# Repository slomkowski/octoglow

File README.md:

# Octoglow VFD - Fallout-inspired post-apocalyptic display

Design files of Octoglow, the post-apocalyptic desktop display device. Detailed article [published on my website](https://slomkowski.eu/octoglow-vfd-fallout-inspired-display/).

(C) Michał Słomkowski

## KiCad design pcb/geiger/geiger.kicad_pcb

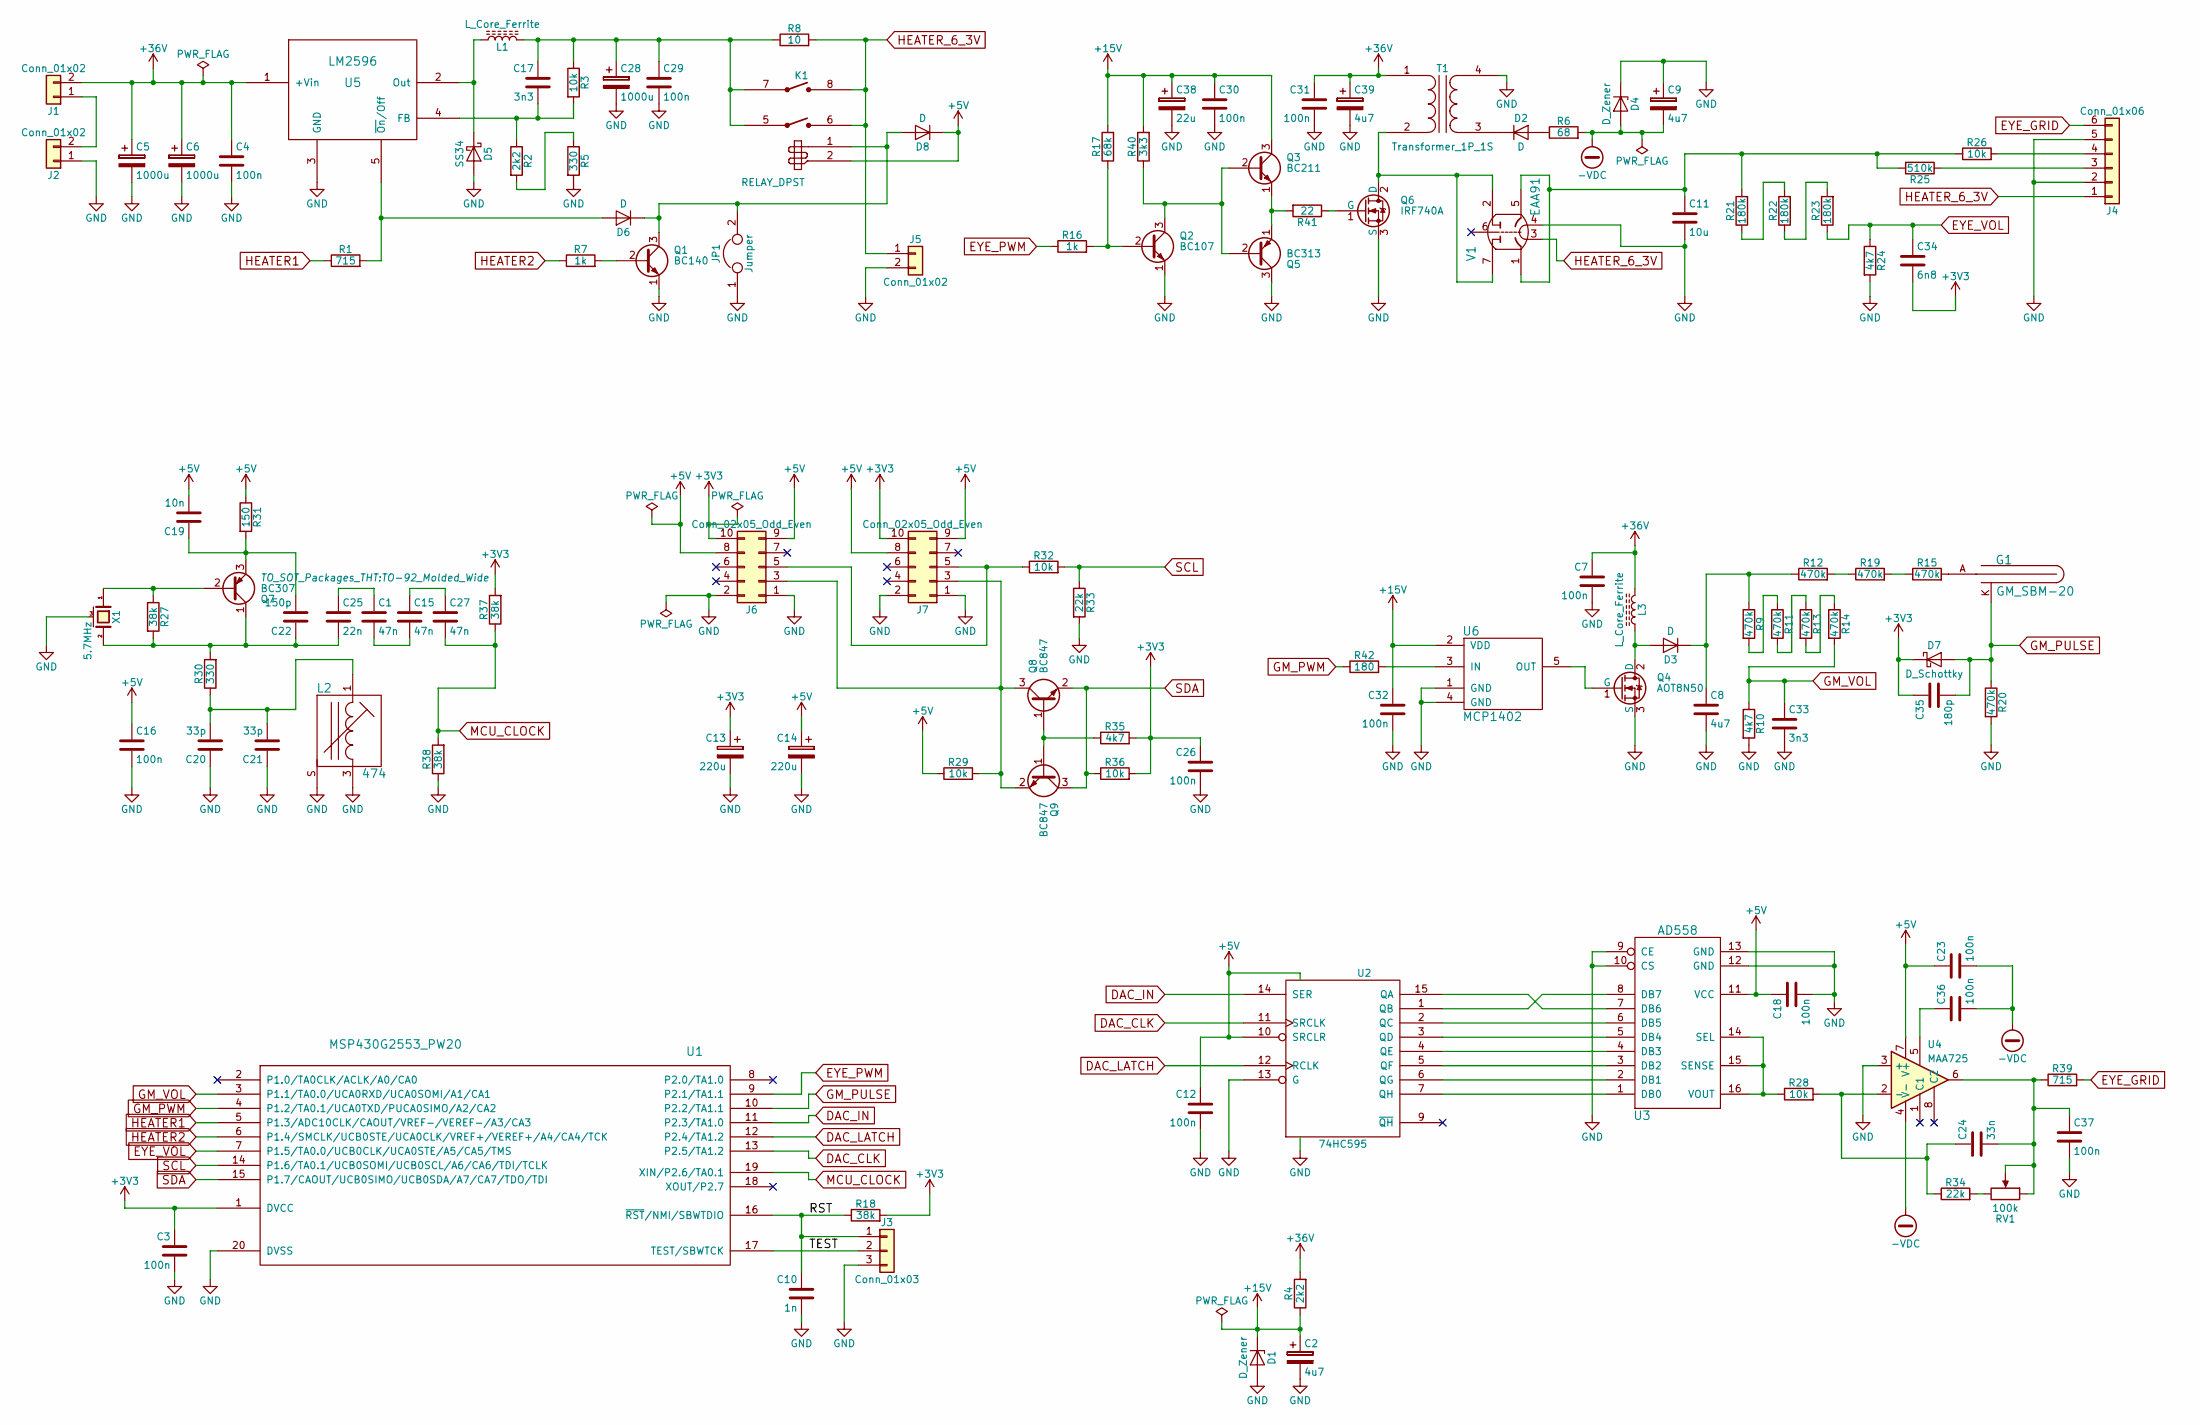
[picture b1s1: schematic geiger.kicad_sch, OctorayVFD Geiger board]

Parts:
C1, C15, C27: 47n; C_Disc_D5.0mm_W2.5mm_P5.00mm
C2: 4u7; CP_Radial_D6.3mm_P2.50mm
C3, C4, C7, C12, C16, C18, C23, C26, C29, C30, C31, C32, C36, C37: 100n; C_1206_HandSoldering
C5, C6: 1000u; CP_Radial_D16.0mm_P7.50mm
C8: 4u7; C_Rect_L33.0mm_W13.0mm_P27.50mm_MKS4
C9, C39: 4u7; CP_Tantalum_Case-D_EIA-7343-31_Hand
C10: 1n; C_0805_HandSoldering
C11: 10u; C_Rect_L33.0mm_W13.0mm_P27.50mm_MKS4
C13, C14: 220u; CP_Radial_D13.0mm_P5.00mm
C17, C33: 3n3; C_1206_HandSoldering
C19: 10n; C_Disc_D5.0mm_W2.5mm_P5.00mm
C20, C21: 33p; C_Disc_D5.0mm_W2.5mm_P5.00mm
C22: 150p; C_Disc_D5.0mm_W2.5mm_P5.00mm
C24: 33n; C_Disc_D11.0mm_W5.0mm_P5.00mm
C25: 22n; C_Disc_D5.0mm_W2.5mm_P5.00mm
C28: 1000u; CP_Radial_D8.0mm_P3.50mm
C34: 6n8; C_Rect_L9.0mm_W3.2mm_P7.50mm_MKT
C35: 180p; C_Rect_L9.0mm_W3.2mm_P7.50mm_MKT
C38: 22u; CP_Tantalum_Case-B_EIA-3528-21_Hand
D1, D4: D_Zener; D_DO-41_SOD81_P2.54mm_Vertical_AnodeUp
D2, D3: D; D_SMB
D5: SS34; D_SMA-SMB_Universal_Handsoldering
D6, D8: D; D_DO-41_SOD81_P12.70mm_Horizontal
D7: D_Schottky; D_DO-35_SOD27_P10.16mm_Horizontal
G1: GM_SBM-20
J1, J2, J5: Conn_01x02; TerminalBlock_Pheonix_MKDS1.5-2pol
J3: Conn_01x03; Pin_Header_Straight_1x03_Pitch2.54mm
J4: Conn_01x06; TerminalBlock_Pheonix_PT-3.5mm_6pol
J6, J7: Conn_02x05_Odd_Even; Pin_Header_Straight_2x05_Pitch2.54mm
JP1: Jumper; Pin_Header_Straight_1x02_Pitch2.54mm
K1: RELAY_DPST; RELAY_DPST_Telfa_K-8
L1: L_Core_Ferrite; Choke_SMD_12x12mm_h8mm
L2: 474; L_7x7_II
L3: L_Core_Ferrite; F1001_coil
Q1: BC140; TO-39-3
Q2: BC107; TO-18-3
Q3: BC211; TO-39-3
Q4: AOT8N50; TO-220-3_Vertical
Q5: BC313; TO-39-3
Q6: IRF740A; TO-220-3_Vertical
Q7: BC307; TO-92_Molded_Wide
Q8, Q9: BC847; SOT-23
R1: 715; R_Axial_DIN0411_L9.9mm_D3.6mm_P12.70mm_Horizontal
R2: 2k2; R_1206_HandSoldering
R3, R29, R32, R36: 10k; R_1206_HandSoldering
R4: 2k2; R_Axial_DIN0207_L6.3mm_D2.5mm_P10.16mm_Horizontal
R5: 330; R_1206_HandSoldering
R6: 68; R_Axial_DIN0309_L9.0mm_D3.2mm_P12.70mm_Horizontal
R7, R16: 1k; R_Axial_DIN0207_L6.3mm_D2.5mm_P10.16mm_Horizontal
R8: 10; R_Axial_DIN0617_L17.0mm_D6.0mm_P30.48mm_Horizontal
R9, R11, R13, R14, R20: 470k; R_1206_HandSoldering
R10, R24, R35: 4k7; R_1206_HandSoldering
R12, R15, R19: 470k; R_Axial_DIN0309_L9.0mm_D3.2mm_P12.70mm_Horizontal
R17: 68k; R_Axial_DIN0207_L6.3mm_D2.5mm_P10.16mm_Horizontal
R18, R27, R37, R38: 38k; R_1206_HandSoldering
R21, R22, R23: 180k; R_0805_HandSoldering
R25: 510k; R_Axial_DIN0309_L9.0mm_D3.2mm_P15.24mm_Horizontal
R26: 10k; R_Axial_DIN0309_L9.0mm_D3.2mm_P15.24mm_Horizontal
R28: 10k; R_Axial_DIN0207_L6.3mm_D2.5mm_P10.16mm_Horizontal
R30: 330; R_Axial_DIN0207_L6.3mm_D2.5mm_P10.16mm_Horizontal
R31: 150; R_Axial_DIN0207_L6.3mm_D2.5mm_P10.16mm_Horizontal
R33: 22k; R_1206_HandSoldering
R34: 22k; R_Axial_DIN0207_L6.3mm_D2.5mm_P10.16mm_Horizontal
R39: 715; R_Axial_DIN0309_L9.0mm_D3.2mm_P12.70mm_Horizontal
R40: 3k3; R_Axial_DIN0207_L6.3mm_D2.5mm_P10.16mm_Horizontal
R41: 22; R_Axial_DIN0309_L9.0mm_D3.2mm_P12.70mm_Horizontal
R42: 180; R_Axial_DIN0309_L9.0mm_D3.2mm_P15.24mm_Horizontal
RV1: 100k; Potentiometer_Trimmer_Bourns_3006P
T1: Transformer_1P_1S; F1001_trans
U1: MSP430G2553_PW20; DIP-20_W7.62mm_LongPads
U2: 74HC595; DIP-16_W7.62mm_LongPads
U3: AD558; DIP-16_W7.62mm_LongPads
U4: MAA725; TO-5-8_H08C
U5: LM2596; TO-263-5_TabPin3
U6: MCP1402; SOT-23-5_HandSoldering
V1: EAA91; HEPTAL1
X1: 5.7MHz; glass_xtal

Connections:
+3V3: C3.1, C13.1, C26.1, C34.2, C35.1, D7.1 (K), J6.10, J7.10, R18.2, R35.2, R36.2, R37.2, U1.1 (DVCC)
+5V: C12.1, C14.1, C16.1, C18.1, C19.2, C23.1, D8.1 (K), J6.8, J6.9, J7.8, J7.9, K1.2, R29.1, R31.1, U2.10 (SRCLR), U2.16 (VCC), U3.11 (VCC), U4.7 (V+)
+15V: C2.1, C30.1, C32.1, C38.1, D1.1 (K), Q3.3 (C), R4.1, R17.2, R40.2, U6.2 (VDD)
+36V: C4.1, C5.1, C6.1, C7.1, C31.1, C39.1, J1.2, L3.2, R4.2, T1.1 (AA), U5.1 (+Vin)
-VDC: C9.2, C23.2, C36.2, D4.2 (A), R6.2, U4.4 (V-)
/RST: C10.1, J3.1, R18.1, U1.16 (~RST/NMI/SBWTDIO)
/TEST: J3.2, U1.17 (TEST/SBWTCK)
DAC_CLK: U1.13 (P2.5/TA1.2), U2.11 (SRCLK)
DAC_IN: U1.11 (P2.3/TA1.0), U2.14 (SER)
DAC_LATCH: U1.12 (P2.4/TA1.2), U2.12 (RCLK)
EYE_GRID: J4.6, R39.2
EYE_PWM: R16.1, U1.9 (P2.1/TA1.1)
EYE_VOL: C34.1, R23.1, R24.1, U1.7 (P1.5/TA0.0/UCB0CLK/UCA0STE/A5/CA5/TMS)
GM_PULSE: C35.2, D7.2 (A), G1.K, R20.1, U1.10 (P2.2/TA1.1)
GM_PWM: R42.1, U1.4 (P1.2/TA0.1/UCA0TXD/PUCA0SIMO/A2/CA2)
GM_VOL: C33.1, R10.1, R14.2, U1.3 (P1.1/TA0.0/UCA0RXD/UCA0SOMI/A1/CA1)
GND: C2.2, C3.2, C4.2, C5.2, C6.2, C7.2, C8.2, C9.1, C10.2, C11.2, C12.2, C13.2, C14.2, C16.2, C18.2, C20.1, C21.1, C26.2, C28.2, C29.2, C30.2, C31.2, C32.2, C33.2, C37.2, C38.2, C39.2, D1.2 (A), D4.1 (K), D5.2 (A), J2.1, J3.3, J4.2, J4.5, J5.2, J6.1, J6.2, J7.1, J7.2, JP1.1, L2.3, L2.S, Q1.1 (E), Q2.1 (E), Q4.3 (S), Q5.3 (C), Q6.3 (S), R5.2, R10.2, R20.2, R24.2, R33.2, R38.1, T1.4 (SB), U1.20 (DVSS), U2.8 (GND), U2.13 (G), U3.9 (CE), U3.10 (CS), U3.12 (GND), U3.13 (GND), U4.3 (+), U5.3 (GND), U6.1 (GND), U6.4 (GND), V1.4, X1.3 (case)
HEATER1: R1.1, U1.5 (P1.3/ADC10CLK/CAOUT/VREF-/VEREF-/A3/CA3)
HEATER2: R7.1, U1.6 (P1.4/SMCLK/UCB0STE/UCA0CLK/VREF+/VEREF+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)
HEATER_6_3V: J4.1, J5.1, K1.6, K1.8, R8.2, V1.3
MCU_CLOCK: C27.2, R37.1, R38.2, U1.19 (XIN/P2.6/TA0.1)
unnamed: C1.1, C25.1
unnamed: C1.2, C15.2
unnamed: C11.1, R21.2, R25.2, R26.1, V1.1, V1.5
unnamed: C15.1, C27.1
unnamed: C17.1, C28.1, C29.1, K1.5, K1.7, L1.2, R3.1, R8.1
unnamed: C20.2, C21.2, L2.1, R30.1
unnamed: C24.2, C37.1, R39.1, RV1.1, RV1.2, U4.6
unnamed: C36.1, U4.5
unnamed: D2.2 (A), R6.1
unnamed: D2.1 (K), T1.3 (SA)
unnamed: D3.2 (A), L3.1, Q4.2 (D)
unnamed: C8.1, D3.1 (K), R9.1, R12.1
unnamed: D5.1 (K), L1.1, U5.2 (Out)
unnamed: D6.2 (A), R1.2, U5.5 (~On/Off)
unnamed: D6.1 (K), D8.2 (A), JP1.2, K1.1, Q1.3 (C)
unnamed: G1.A, R15.2
unnamed: J1.1, J2.2
unnamed: J4.3, R25.1
unnamed: J4.4, R26.2
unnamed: J6.3, J7.3, Q8.3 (C), Q9.2 (E), R29.2
unnamed: J6.5, J7.5, R32.1
unnamed: Q1.2 (B), R7.2
unnamed: Q2.2 (B), R16.2, R17.1
unnamed: Q2.3 (C), Q3.2 (B), Q5.2 (B), R40.1
unnamed: Q3.1 (E), Q5.1 (E), R41.2
unnamed: Q4.1 (G), U6.5 (OUT)
unnamed: Q6.2 (D), T1.2 (AB), V1.2, V1.7
unnamed: Q6.1 (G), R41.1
unnamed: Q7.2 (B), R27.1, X1.1
unnamed: C22.1, C25.2, Q7.1 (C), R27.2, R30.2, X1.2
unnamed: C19.1, C22.2, Q7.3 (E), R31.2
unnamed: Q8.1 (B), Q9.1 (B), R35.1
unnamed: R2.2, R5.1
unnamed: R9.2, R11.1
unnamed: R11.2, R13.1
unnamed: R12.2, R19.1
unnamed: R13.2, R14.1
unnamed: R15.1, R19.2
unnamed: R21.1, R22.2
unnamed: R22.1, R23.2
unnamed: R34.2, RV1.3
unnamed: U2.15 (QA), U3.7 (DB6)
unnamed: U2.1 (QB), U3.8 (DB7)
unnamed: U2.2 (QC), U3.6 (DB5)
unnamed: U2.3 (QD), U3.5 (DB4)
unnamed: U2.4 (QE), U3.4 (DB3)
unnamed: U2.5 (QF), U3.3 (DB2)
unnamed: U2.6 (QG), U3.2 (DB1)
unnamed: U2.7 (QH), U3.1 (DB0)
unnamed: R28.1, U3.14 (SEL), U3.15 (SENSE), U3.16 (VOUT)
unnamed: C24.1, R28.2, R34.1, U4.2 (-)
unnamed: C17.2, R2.1, R3.2, U5.4 (FB)
unnamed: R42.2, U6.3 (IN)
SCL: R32.2, R33.1, U1.14 (P1.6/TA0.1/UCB0SOMI/UCB0SCL/A6/CA6/TDI/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)
SDA: Q8.2 (E), Q9.3 (C), R36.1, U1.15 (P1.7/CAOUT/UCB0SIMO/UCB0SDA/A7/CA7/TDO/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)

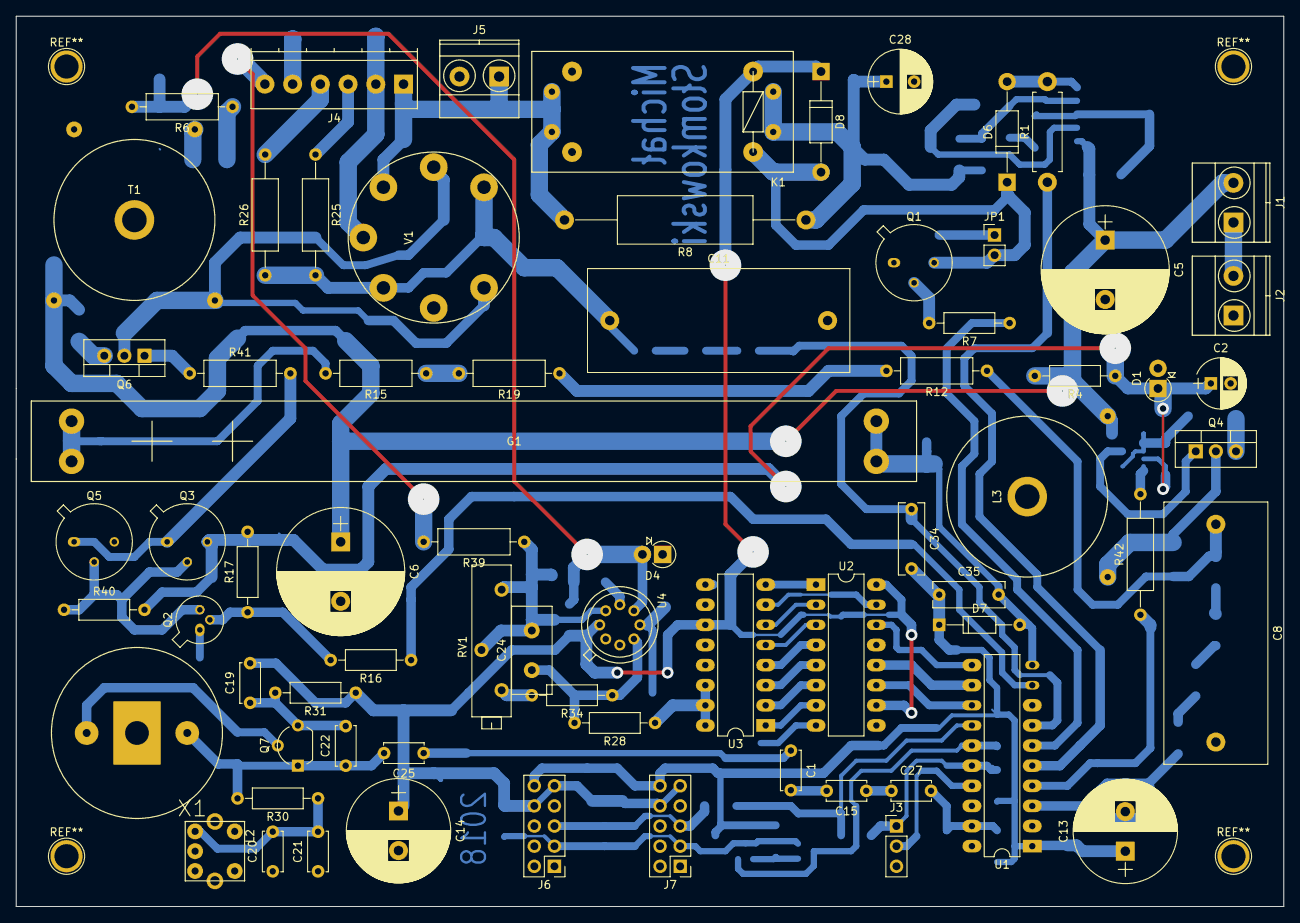
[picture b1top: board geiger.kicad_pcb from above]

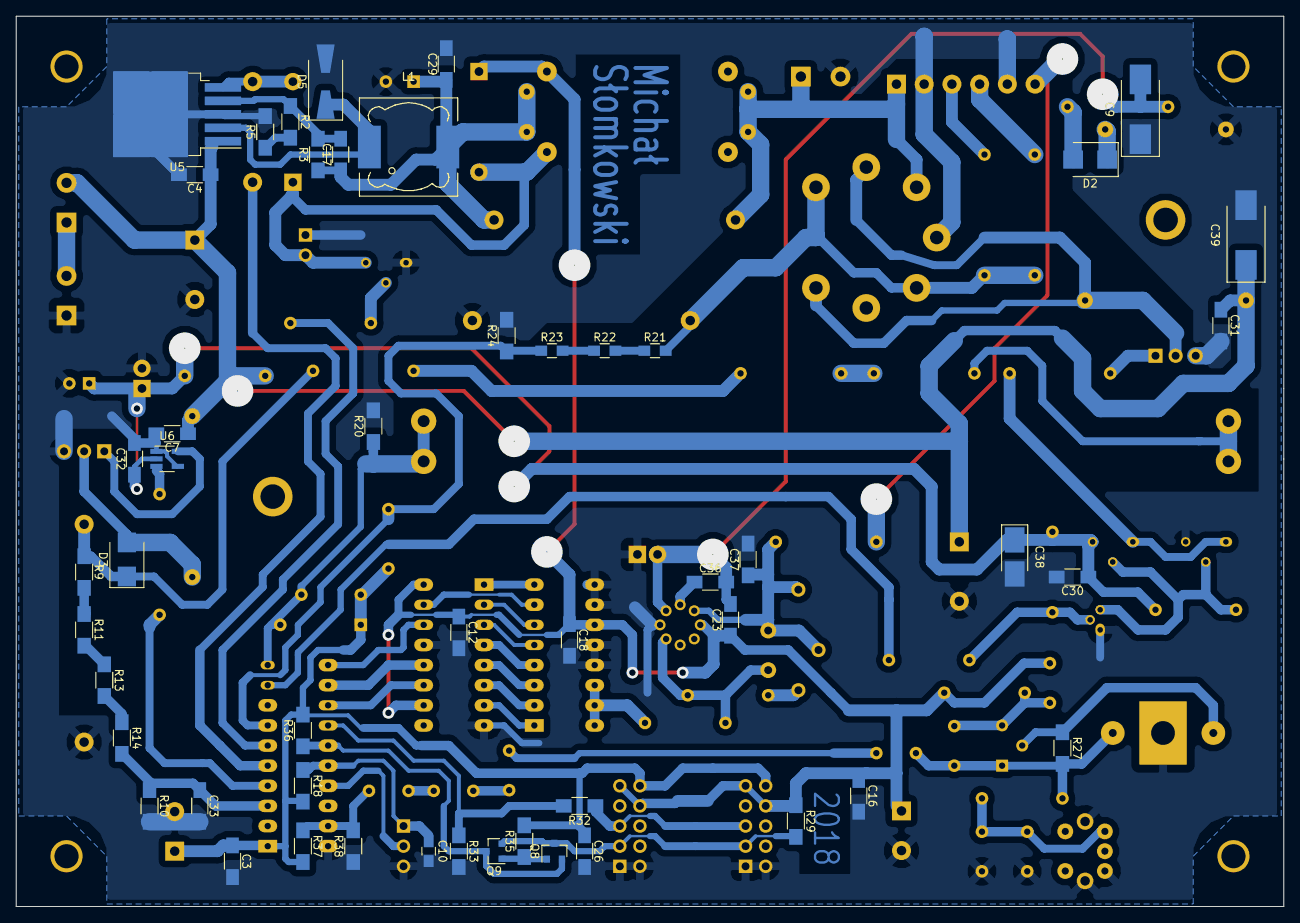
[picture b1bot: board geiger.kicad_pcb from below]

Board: 2 copper layers, 160.0 x 112.4 mm, 121 parts (50 on the bottom side), 76 nets.

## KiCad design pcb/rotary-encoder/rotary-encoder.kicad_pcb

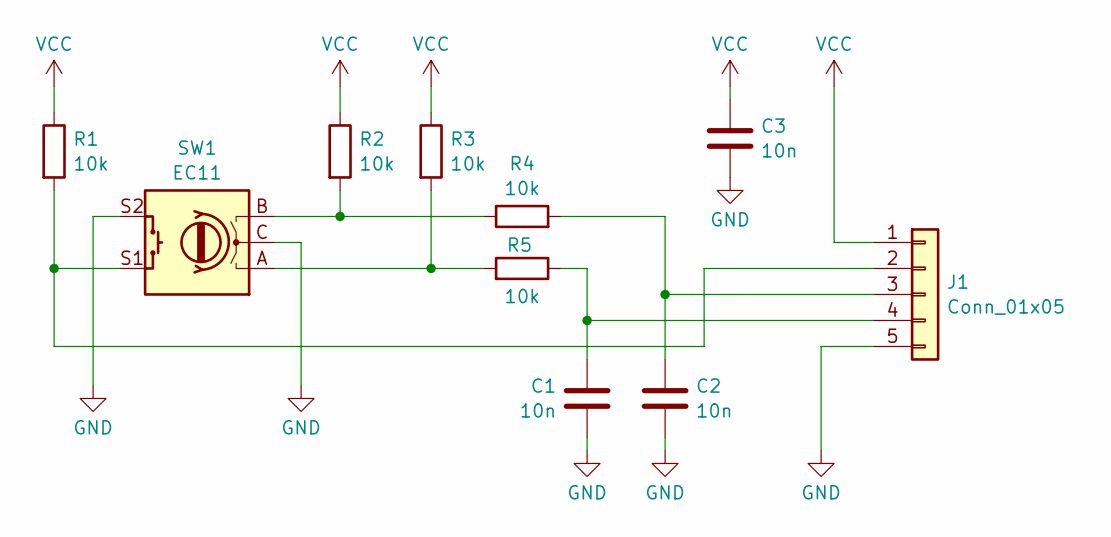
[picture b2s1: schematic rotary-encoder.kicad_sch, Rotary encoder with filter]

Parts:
C1, C2, C3: 10n; C_1206_3216Metric_Pad1.33x1.80mm_HandSolder
J1: Conn_01x05; PinHeader_1x05_P2.54mm_Horizontal
R1, R2, R3, R4, R5: 10k; R_1206_3216Metric_Pad1.30x1.75mm_HandSolder
SW1: EC11; RotaryEncoder_Alps_EC12E-Switch_Vertical_H20mm

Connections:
GND: C1.2, C2.2, C3.2, J1.5, SW1.C, SW1.S2
unnamed: J1.2, R1.2, SW1.S1
unnamed: C2.1, J1.3, R4.2
unnamed: C1.1, J1.4, R5.1
unnamed: R2.2, R4.1, SW1.B
unnamed: R3.2, R5.2, SW1.A
VCC: C3.1, J1.1, R1.1, R2.1, R3.1

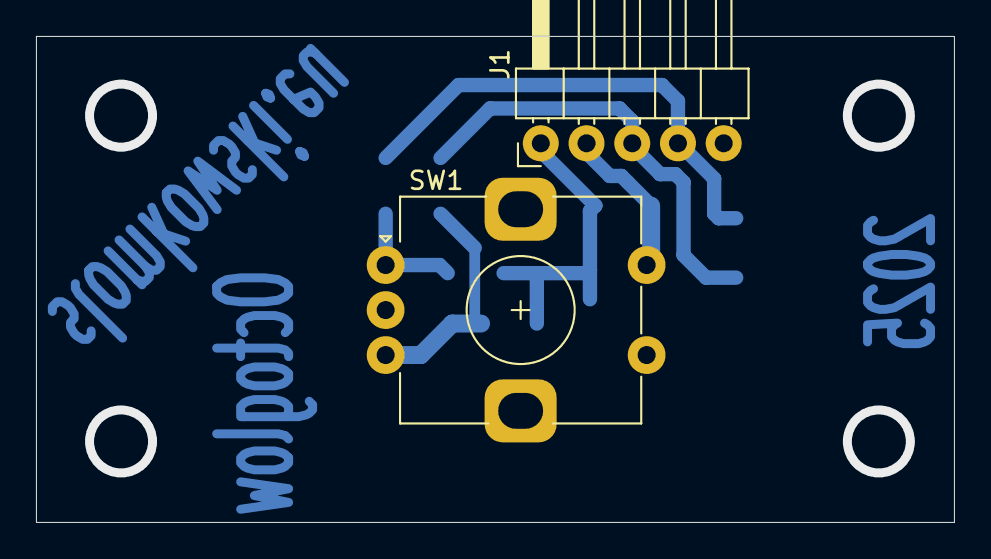
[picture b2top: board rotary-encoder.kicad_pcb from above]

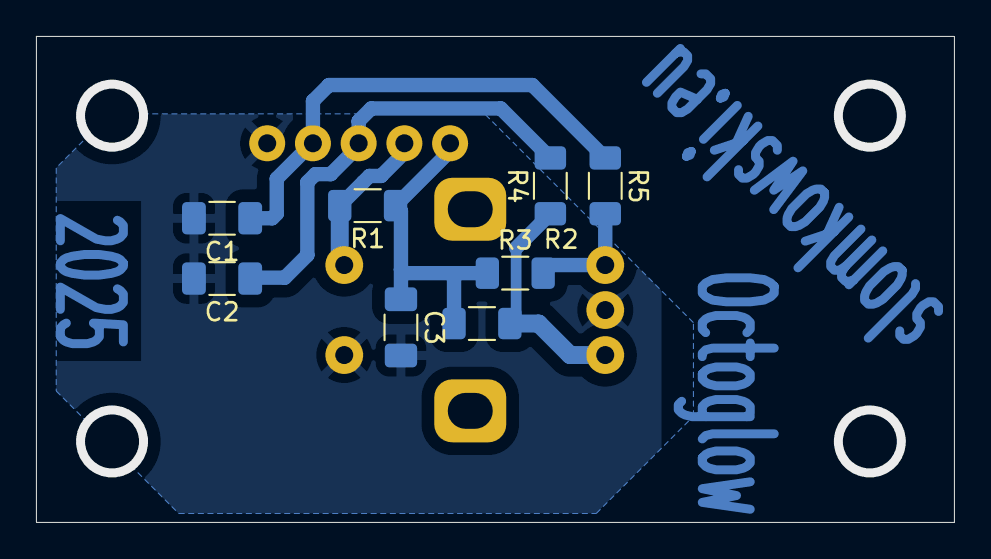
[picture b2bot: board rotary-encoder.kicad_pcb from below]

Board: 2 copper layers, 51.0 x 27.0 mm, 10 parts (8 on the bottom side), 7 nets.

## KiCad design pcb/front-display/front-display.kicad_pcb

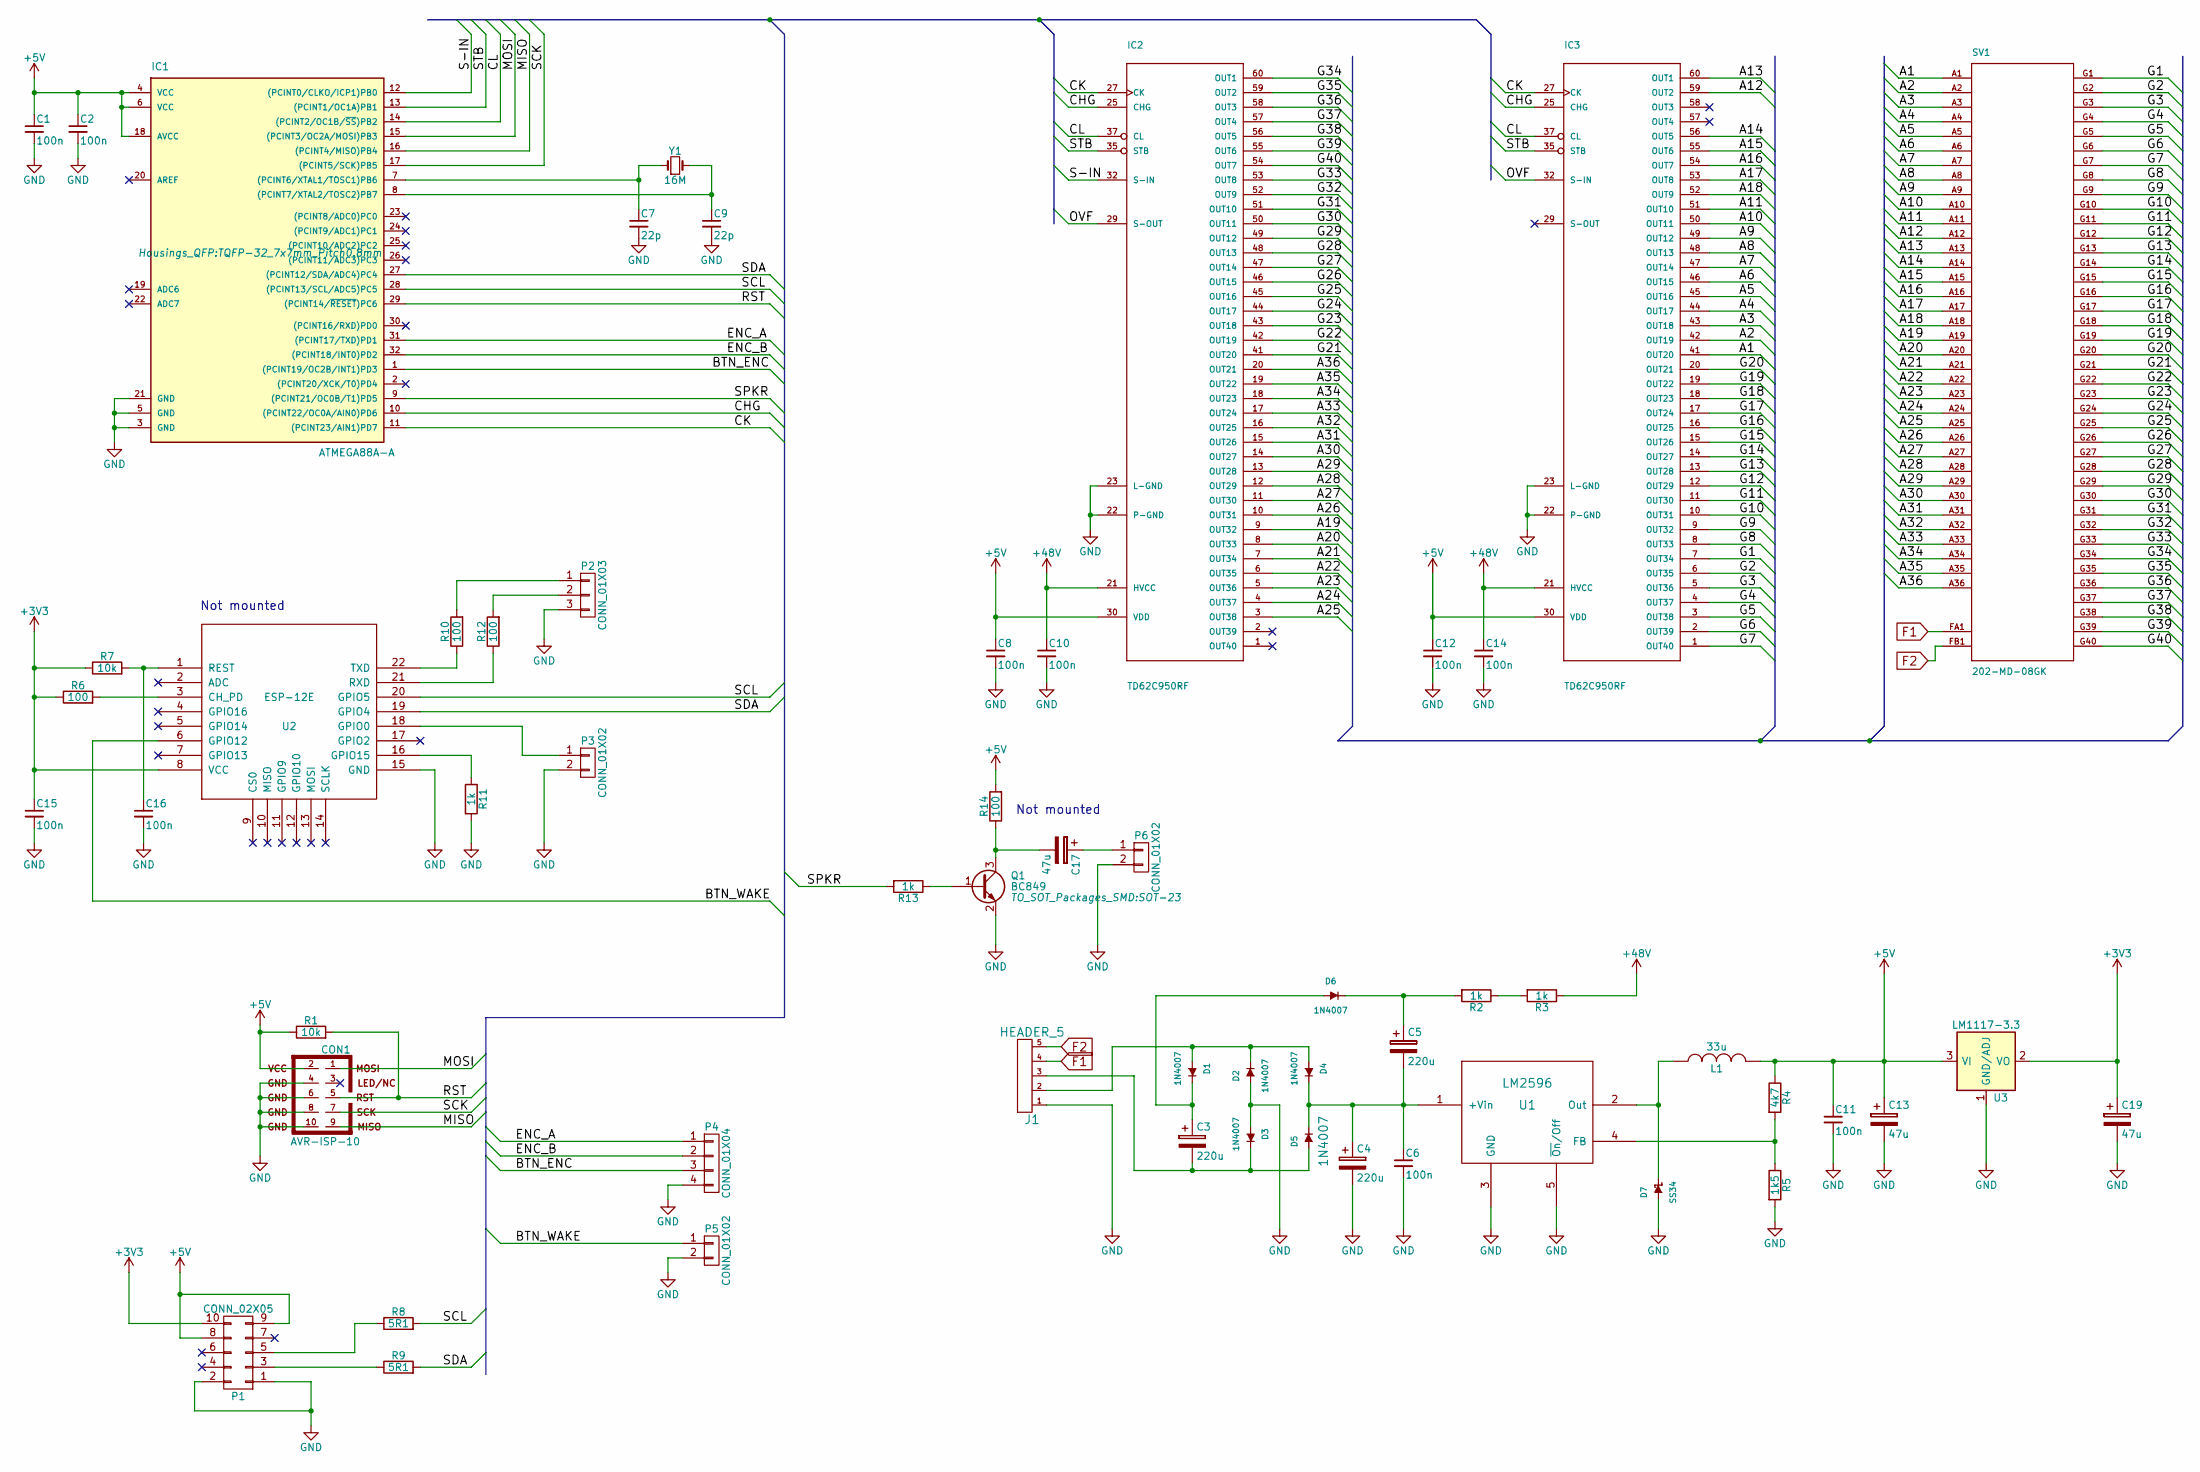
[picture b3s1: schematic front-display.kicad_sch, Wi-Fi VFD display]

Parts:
C1, C2, C6, C8, C10, C11, C12, C14, C15, C16: 100n; C_1206_HandSoldering
C3, C4, C5: 220u; c_elec_10x10
C7, C9: 22p; C_0805_HandSoldering
C13, C17, C19: 47u; c_elec_8x10.5
CON1: AVR-ISP-10; Pin_Header_Straight_2x05
D1, D2, D3, D4, D5, D6: 1N4007; SMA-SMB_Universal_Handsoldering
D7: SS34; SMA-SMB_Universal_Handsoldering
IC1: ATMEGA88A-A; TQFP-32_7x7mm_Pitch0.8mm
IC2, IC3: TD62C950RF; TD62C950RF-SSOP60-P-0.65A
J1: HEADER_5; TerminalBlock_Pheonix_MKDS1.5-5pol
L1: 33u; Choke_SMD_12x12mm_h8mm
P1: CONN_02X05; Pin_Header_Straight_2x05
P2: CONN_01X03; Pin_Header_Straight_1x03
P3, P5, P6: CONN_01X02; Pin_Header_Straight_1x02
P4: CONN_01X04; Pin_Header_Straight_1x04
Q1: BC849; SOT-23
R1, R7: 10k; R_1206_HandSoldering
R2, R3, R11, R13: 1k; R_1206_HandSoldering
R4: 4k7; R_1206_HandSoldering
R5: 1k5; R_1206_HandSoldering
R6, R10, R12, R14: 100; R_1206_HandSoldering
R8, R9: 5R1; R_1206_HandSoldering
SV1: 202-MD-08GK; futaba-vfd-VFD1
U1: LM2596; TO-263-5Lead
U2: ESP-12E
U3: LM1117-3.3; SOT-223
Y1: 16M; crystal-hc49sm

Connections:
+3V3: C15.1, C19.1, P1.10, R6.1, R7.1, U2.8 (VCC), U3.2 (VO), U3.4 (VO)
+5V: C1.1, C2.1, C8.1, C11.1, C12.1, C13.1, CON1.2, IC1.4 (VCC), IC1.6 (VCC), IC1.18 (AVCC), IC2.30 (VDD), IC2.31 (VDD), IC3.30 (VDD), IC3.31 (VDD), L1.2, P1.8, P1.9, R1.1, R4.1, R14.2, U3.3 (VI)
+48V: C10.1, C14.1, IC2.21 (HVCC), IC2.40 (HVCC), IC3.21 (HVCC), IC3.40 (HVCC), R3.1
/A1: IC3.41 (OUT20), SV1.A1
/A2: IC3.42 (OUT19), SV1.A2
/A3: IC3.43 (OUT18), SV1.A3
/A4: IC3.44 (OUT17), SV1.A4
/A5: IC3.45 (OUT16), SV1.A5
/A6: IC3.46 (OUT15), SV1.A6
/A7: IC3.47 (OUT14), SV1.A7
/A8: IC3.48 (OUT13), SV1.A8
/A9: IC3.49 (OUT12), SV1.A9
/A10: IC3.50 (OUT11), SV1.A10
/A11: IC3.51 (OUT10), SV1.A11
/A12: IC3.59 (OUT2), SV1.A12
/A13: IC3.60 (OUT1), SV1.A13
/A14: IC3.56 (OUT5), SV1.A14
/A15: IC3.55 (OUT6), SV1.A15
/A16: IC3.54 (OUT7), SV1.A16
/A17: IC3.53 (OUT8), SV1.A17
/A18: IC3.52 (OUT9), SV1.A18
/A19: IC2.9 (OUT32), SV1.A19
/A20: IC2.8 (OUT33), SV1.A20
/A21: IC2.7 (OUT34), SV1.A21
/A22: IC2.6 (OUT35), SV1.A22
/A23: IC2.5 (OUT36), SV1.A23
/A24: IC2.4 (OUT37), SV1.A24
/A25: IC2.3 (OUT38), SV1.A25
/A26: IC2.10 (OUT31), SV1.A26
/A27: IC2.11 (OUT30), SV1.A27
/A28: IC2.12 (OUT29), SV1.A28
/A29: IC2.13 (OUT28), SV1.A29
/A30: IC2.14 (OUT27), SV1.A30
/A31: IC2.15 (OUT26), SV1.A31
/A32: IC2.16 (OUT25), SV1.A32
/A33: IC2.17 (OUT24), SV1.A33
/A34: IC2.18 (OUT23), SV1.A34
/A35: IC2.19 (OUT22), SV1.A35
/A36: IC2.20 (OUT21), SV1.A36
/BTN_ENC: IC1.1 ((PCINT19/OC2B/INT1)PD3), P4.3
/BTN_WAKE: P5.1, U2.6 (GPIO12)
/CHG: IC1.10 ((PCINT22/OC0A/AIN0)PD6), IC2.25 (CHG), IC3.25 (CHG)
/CK: IC1.11 ((PCINT23/AIN1)PD7), IC2.27 (CK), IC3.27 (CK)
/CL: IC1.14 ((PCINT2/OC1B/~SS)PB2), IC2.37 (CL), IC3.37 (CL)
/ENC_A: IC1.31 ((PCINT17/TXD)PD1), P4.1
/ENC_B: IC1.32 ((PCINT18/INT0)PD2), P4.2
/G1: IC3.7 (OUT34), SV1.G1
/G2: IC3.6 (OUT35), SV1.G2
/G3: IC3.5 (OUT36), SV1.G3
/G4: IC3.4 (OUT37), SV1.G4
/G5: IC3.3 (OUT38), SV1.G5
/G6: IC3.2 (OUT39), SV1.G6
/G7: IC3.1 (OUT40), SV1.G7
/G8: IC3.8 (OUT33), SV1.G8
/G9: IC3.9 (OUT32), SV1.G9
/G10: IC3.10 (OUT31), SV1.G10
/G11: IC3.11 (OUT30), SV1.G11
/G12: IC3.12 (OUT29), SV1.G12
/G13: IC3.13 (OUT28), SV1.G13
/G14: IC3.14 (OUT27), SV1.G14
/G15: IC3.15 (OUT26), SV1.G15
/G16: IC3.16 (OUT25), SV1.G16
/G17: IC3.17 (OUT24), SV1.G17
/G18: IC3.18 (OUT23), SV1.G18
/G19: IC3.19 (OUT22), SV1.G19
/G20: IC3.20 (OUT21), SV1.G20
/G21: IC2.41 (OUT20), SV1.G21
/G22: IC2.42 (OUT19), SV1.G22
/G23: IC2.43 (OUT18), SV1.G23
/G24: IC2.44 (OUT17), SV1.G24
/G25: IC2.45 (OUT16), SV1.G25
/G26: IC2.46 (OUT15), SV1.G26
/G27: IC2.47 (OUT14), SV1.G27
/G28: IC2.48 (OUT13), SV1.G28
/G29: IC2.49 (OUT12), SV1.G29
/G30: IC2.50 (OUT11), SV1.G30
/G31: IC2.51 (OUT10), SV1.G31
/G32: IC2.52 (OUT9), SV1.G32
/G33: IC2.53 (OUT8), SV1.G33
/G34: IC2.60 (OUT1), SV1.G34
/G35: IC2.59 (OUT2), SV1.G35
/G36: IC2.58 (OUT3), SV1.G36
/G37: IC2.57 (OUT4), SV1.G37
/G38: IC2.56 (OUT5), SV1.G38
/G39: IC2.55 (OUT6), SV1.G39
/G40: IC2.54 (OUT7), SV1.G40
/MISO: CON1.9, IC1.16 ((PCINT4/MISO)PB4)
/MOSI: CON1.1, IC1.15 ((PCINT3/OC2A/MOSI)PB3)
/OVF: IC2.29 (S-OUT), IC3.32 (S-IN)
/RST: CON1.5, IC1.29 ((PCINT14/~RESET)PC6), R1.2
/S-IN: IC1.12 ((PCINT0/CLKO/ICP1)PB0), IC2.32 (S-IN)
/SCK: CON1.7, IC1.17 ((PCINT5/SCK)PB5)
/SCL: IC1.28 ((PCINT13/SCL/ADC5)PC5), R8.2, U2.20 (GPIO5)
/SDA: IC1.27 ((PCINT12/SDA/ADC4)PC4), R9.2, U2.19 (GPIO4)
/SPKR: IC1.9 ((PCINT21/OC0B/T1)PD5), R13.2
/STB: IC1.13 ((PCINT1/OC1A)PB1), IC2.35 (STB), IC3.35 (STB)
F1: J1.4, SV1.FA1 (F1), SV1.FA2 (F1), SV1.FA3 (F1)
F2: J1.5, SV1.FB1 (F2), SV1.FB2 (F2), SV1.FB3 (F2)
GND: C1.2, C2.2, C4.2, C6.2, C7.2, C8.2, C9.2, C10.2, C11.2, C12.2, C13.2, C14.2, C15.2, C16.2, C19.2, CON1.4, CON1.6, CON1.8, CON1.10, D2.1 (A), D3.1 (A), D7.1 (A), IC1.3 (GND), IC1.5 (GND), IC1.21 (GND), IC2.22 (P-GND), IC2.23 (L-GND), IC2.38 (L-GND), IC2.39 (P-GND), IC3.22 (P-GND), IC3.23 (L-GND), IC3.38 (L-GND), IC3.39 (P-GND), J1.1, P1.1, P1.2, P2.3, P3.2, P4.4, P5.2, P6.2, Q1.2 (E), R5.2, R11.2, U1.3 (GND), U1.5 (~On/Off), U2.15 (GND), U3.1 (GND/ADJ)
unnamed: D1.1 (A), D2.2 (K), D4.1 (A), J1.2
unnamed: C3.1, D1.2 (K), D6.1 (A)
unnamed: C3.2, D3.2 (K), D5.1 (A), J1.3
unnamed: C4.1, C5.2, C6.1, D4.2 (K), D5.2 (K), U1.1 (+Vin)
unnamed: C5.1, D6.2 (K), R2.2
unnamed: D7.2 (K), L1.1, U1.2 (Out)
unnamed: C7.1, IC1.7 ((PCINT6/XTAL1/TOSC1)PB6), Y1.1
unnamed: C9.1, IC1.8 ((PCINT7/XTAL2/TOSC2)PB7), Y1.2
unnamed: P1.3, R9.1
unnamed: P1.5, R8.1
unnamed: P2.1, R10.2
unnamed: P2.2, R12.2
unnamed: P3.1, U2.18 (GPIO0)
unnamed: C17.1, P6.1
unnamed: Q1.1 (B), R13.1
unnamed: C17.2, Q1.3 (C), R14.1
unnamed: R2.1, R3.2
unnamed: R4.2, R5.1, U1.4 (FB)
unnamed: R6.2, U2.3 (CH_PD)
unnamed: R11.1, U2.16 (GPIO15)
unnamed: C16.1, R7.2, U2.1 (REST)
unnamed: R12.1, U2.21 (RXD)
unnamed: R10.1, U2.22 (TXD)

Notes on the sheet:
Not mounted
Not mounted

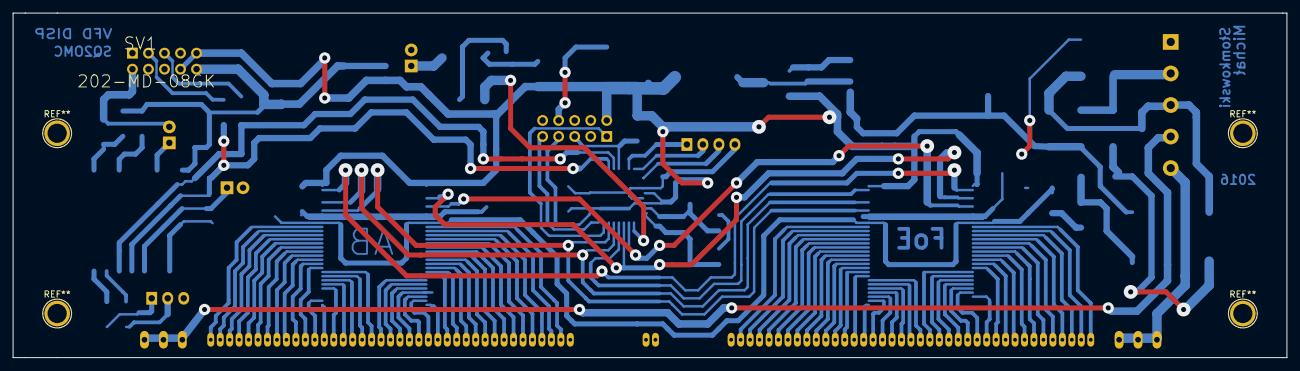
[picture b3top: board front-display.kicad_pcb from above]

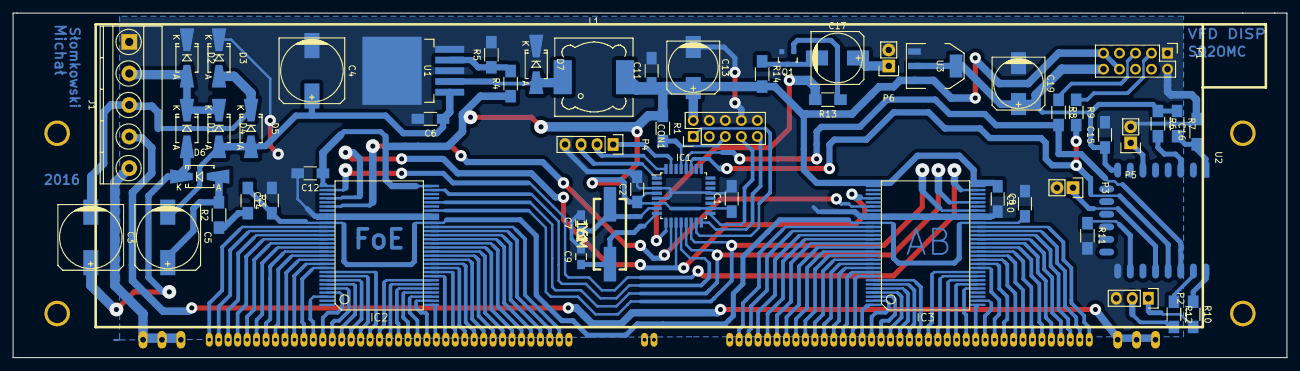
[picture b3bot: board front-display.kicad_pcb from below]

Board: 2 copper layers, 201.9 x 54.6 mm, 57 parts (56 on the bottom side), 122 nets.
